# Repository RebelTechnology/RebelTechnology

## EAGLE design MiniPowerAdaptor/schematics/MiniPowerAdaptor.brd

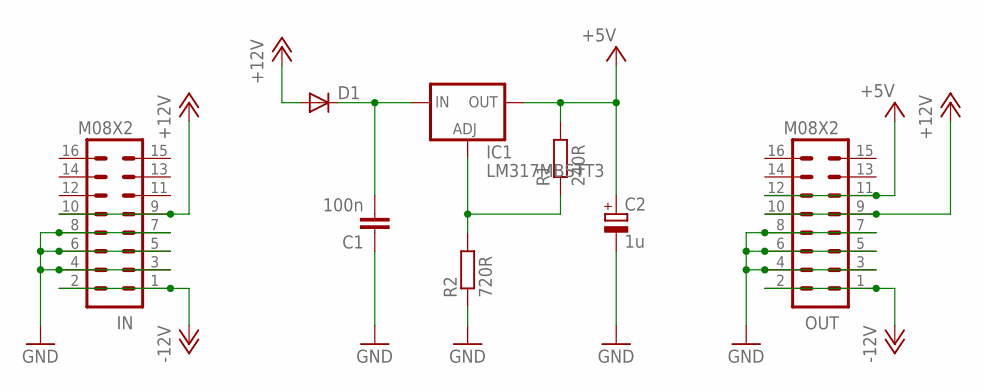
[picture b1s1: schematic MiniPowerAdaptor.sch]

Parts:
C1: 100n; C0603
C2: 1u; SANYO-OSCON_SMD_A5
D1: DIODESMA; SMA-DIODE
IC1: LM317MBSTT3; SOT223
IN: M08X2; 2X8
OUT: M08X2; 2X8
R1: 240R; 0603
R2: 720R; 0603

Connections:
+5V: C2.+, IC1.4 (OUT), OUT.11, OUT.12, R1.2
+12V: D1.A, IN.9, IN.10, OUT.9, OUT.10
-12V: IN.1, IN.2, OUT.1, OUT.2
GND: C1.1, C2.-, IN.3, IN.4, IN.5, IN.6, IN.7, IN.8, OUT.3, OUT.4, OUT.5, OUT.6, OUT.7, OUT.8, R2.1
unnamed: IC1.1 (ADJ), R1.1, R2.2
unnamed: C1.2, D1.C, IC1.3 (IN)

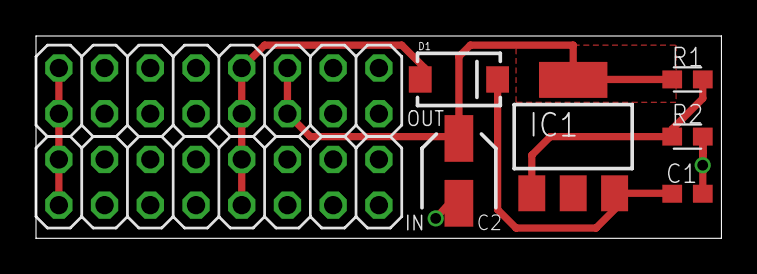
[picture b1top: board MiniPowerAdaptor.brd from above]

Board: 2 copper layers, 38.1 x 11.2 mm, 8 parts (0 on the bottom side), 6 nets.

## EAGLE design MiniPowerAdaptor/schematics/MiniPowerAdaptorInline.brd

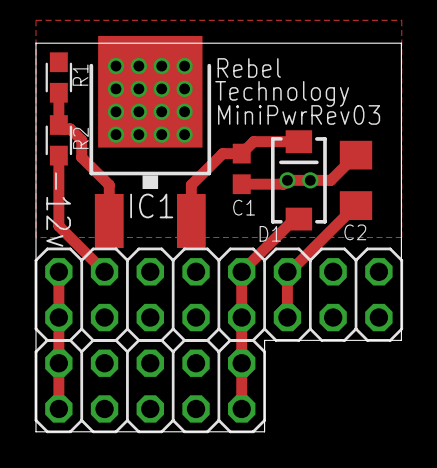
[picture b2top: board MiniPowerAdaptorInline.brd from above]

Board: 2 copper layers, 20.3 x 21.6 mm, 8 parts (0 on the bottom side), 6 nets.

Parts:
C1: 100n; C0603
C2: 10u; C1206
D1: S1J; SMA-DIODE
IC1: LM317; DPACK
JP1: 2X05
OUT: M08X2; 2X8
R1: 330R; 0603
R2: 1k; 0603

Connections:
+5V: C2.1, IC1.4, OUT.11, OUT.12, R1.2
+12V: D1.A, JP1.9, JP1.10, OUT.9, OUT.10
-12V: JP1.1, JP1.2, OUT.1, OUT.2
GND: C1.1, C2.2, JP1.3, JP1.4, JP1.5, JP1.6, JP1.7, JP1.8, OUT.3, OUT.4, OUT.5, OUT.6, OUT.7, OUT.8, R2.1
unnamed: IC1.1, R1.1, R2.2
unnamed: C1.2, D1.C, IC1.3

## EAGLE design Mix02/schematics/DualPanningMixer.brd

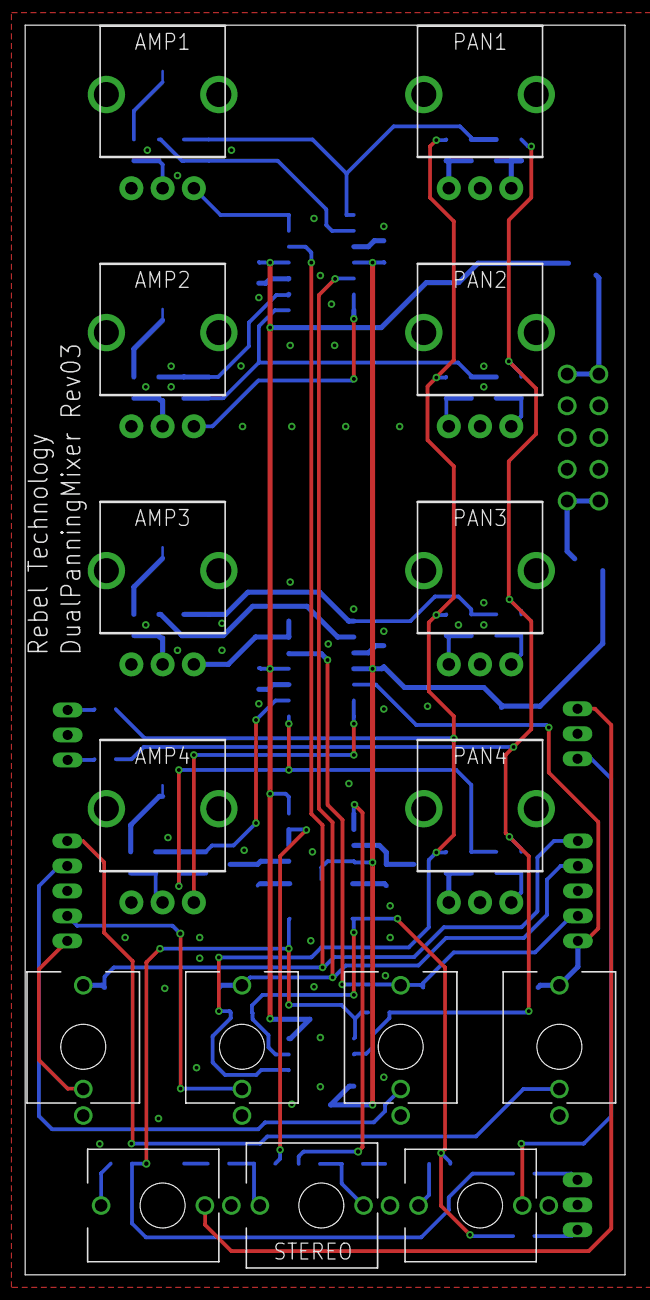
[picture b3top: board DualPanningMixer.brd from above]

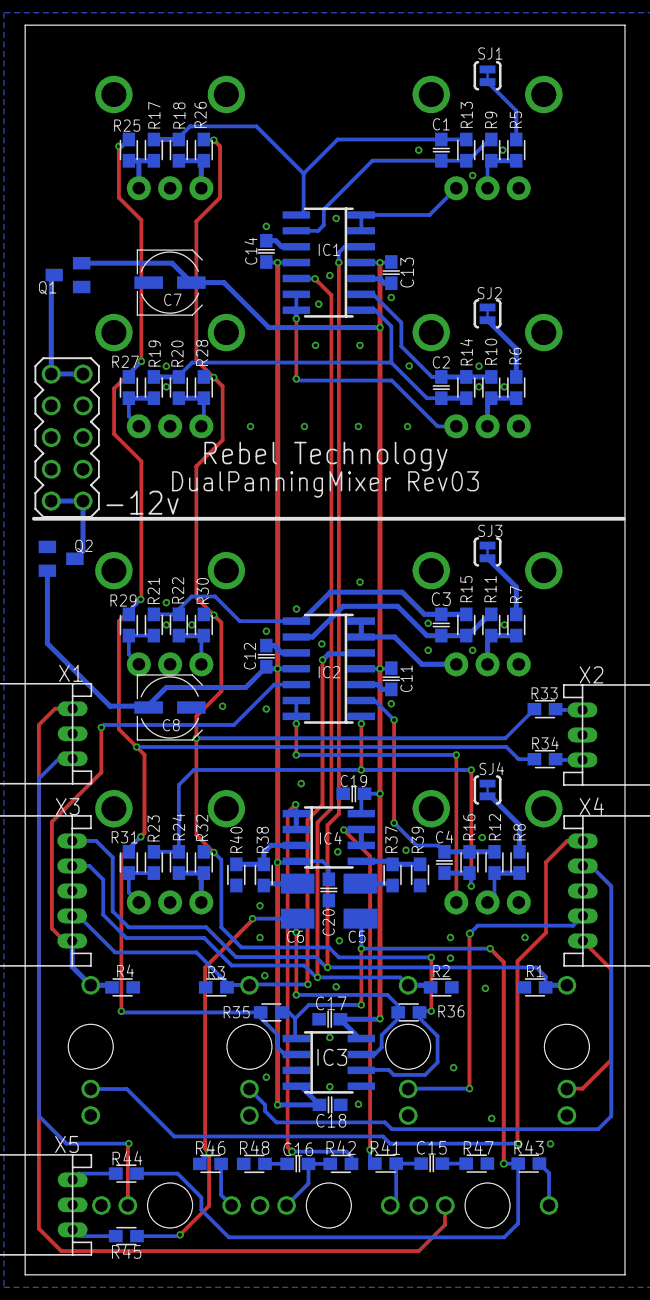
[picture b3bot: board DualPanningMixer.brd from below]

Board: 2 copper layers, 48.0 x 100.0 mm, 97 parts (82 on the bottom side), 63 nets.

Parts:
AMP1, AMP2, AMP3, AMP4: POT-ALPS-RK09L1140
C1, C2, C3, C4: 10p; C0603
C5, C6: 1u Polyester; C1210
C7, C8: 47u; UD-5X5,8_NICHICON
C11, C12, C13, C14, C17, C18, C19, C20: 100n; C0603
C15, C16: 47n; C0603
IC1, IC2: TL074; SO14
IC3: TL072; SO08
IC4: OPA1678; SO08
IN1, IN2, IN3, IN4: THONKICONN
OUTHP: THONKICONN_STEREO
OUTL: THONKICONN
OUTR: THONKICONN
PAN1, PAN2, PAN3, PAN4: POT-ALPS-RK09L1140
Q1: BSS84; SOT23
Q2: BSS123; SOT23
R1, R2, R3, R4: 1M; 0603
R5, R6, R7, R8: 2k7; 0603
R9, R10, R11, R12, R17, R18, R19, R20, R21, R22, R23, R24, R25, R26, R27, R28, R29, R30, R31, R32: 10k; 0603
R13, R14, R15, R16, R35, R36: 22k; 0603
R33, R34: 18k; 0603
R37, R38: 2k; 0603
R39, R40: 1k; 0603
R41, R42, R47, R48: 10R; 0603
R43, R44, R45, R46: 100R; 0603
SJ1, SJ2, SJ3, SJ4: SOLDERJUMPERTRACE; SJ_2S-TRACE
SV1: MA05-2
X1, X2, X5: CON-JST_PH_3W
X3, X4: CON-JST_PH_5W

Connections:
+12V: C7.+, C11.2, C13.2, C17.2, C19.1, IC1.4, IC2.4, IC3.8, IC4.8, Q1.2
-12V: C8.-, C12.2, C14.2, C18.2, C20.1, IC1.11, IC2.11, IC3.4, IC4.4, Q2.2
GND: AMP1.1, AMP1.P$5, AMP1.P$6, AMP2.1, AMP2.P$5, AMP2.P$6, AMP3.1, AMP3.P$5, AMP3.P$6, AMP4.1, AMP4.P$5, AMP4.P$6, C7.-, C8.+, C11.1, C12.1, C13.1, C14.1, C17.1, C18.1, C19.2, C20.2, IC1.3, IC1.10, IC2.3, IC2.10, IC3.3, IC3.5, IN1.P$1, IN2.P$1, IN3.P$1, IN4.P$1, OUTHP.P$1, OUTL.P$1, OUTR.P$1, PAN1.2, PAN1.P$5, PAN1.P$6, PAN2.2, PAN2.P$5, PAN2.P$6, PAN3.2, PAN3.P$5, PAN3.P$6, PAN4.2, PAN4.P$5, PAN4.P$6, Q1.1, Q2.1, R1.1, R2.1, R3.1, R4.1, R39.1, R40.1, R47.1, R48.1, SJ1.1, SJ2.1, SJ3.1, SJ4.1, SV1.3, SV1.4, SV1.5, SV1.6, SV1.7, SV1.8, X1.P2, X2.P2, X3.P3, X4.P3, X5.P2
LAB: IC3.2, R25.1, R27.1, R29.1, R31.1, R34.2, R35.1
L_OUT: C15.1, OUTHP.P$3, R41.1
MONO1: AMP1.3, IC1.6, IC1.7
MONO1_F: IC1.5, IN1.P$3, R1.2, X3.P1
MONO2: AMP2.3, IC1.13, IC1.14
MONO2_F: IC1.12, IN2.P$3, R2.2, X3.P2
MONO3: AMP3.3, IC2.6, IC2.7
MONO3_F: IC2.5, IN3.P$3, R3.2, X3.P4
MONO4: AMP4.3, IC2.13, IC2.14
MONO4_F: IC2.12, IN4.P$3, R4.2, X3.P5
unnamed: AMP4.2, R8.2, R12.1
unnamed: IN2.P$2, X4.P2
unnamed: C5.1, IC3.1, R35.2, R43.1, R44.1
unnamed: IN1.P$2, X4.P1
unnamed: C6.1, IC3.7, R36.2, R45.1, R46.1
unnamed: IN3.P$2, X4.P4
unnamed: IC4.3, R38.1, R40.2
unnamed: AMP1.2, R5.2, R9.1
unnamed: C1.2, IC1.9, R9.2, R13.1
unnamed: AMP3.2, R7.2, R11.1
unnamed: AMP2.2, R6.2, R10.1
unnamed: R5.1, SJ1.2
unnamed: IC4.5, R37.1, R39.2
unnamed: R33.1, X2.P3
unnamed: IN4.P$2, X4.P5
unnamed: R6.1, SJ2.2
unnamed: PAN1.1, R18.1, R26.2
unnamed: PAN1.3, R17.1, R25.2
unnamed: R7.1, SJ3.2
unnamed: R8.1, SJ4.2
unnamed: C1.1, IC1.8, R13.2, R17.2, R18.2
unnamed: R34.1, X2.P1
unnamed: C4.1, IC2.1, R16.2, R23.2, R24.2
unnamed: C2.1, IC1.1, R14.2, R19.2, R20.2
unnamed: PAN2.3, R19.1, R27.2
unnamed: OUTL.P$3, R43.2
unnamed: PAN2.1, R20.1, R28.2
unnamed: PAN3.3, R21.1, R29.2
unnamed: C3.1, IC2.8, R15.2, R21.2, R22.2
unnamed: PAN3.1, R22.1, R30.2
unnamed: PAN4.3, R23.1, R31.2
unnamed: OUTR.P$3, R46.2
unnamed: PAN4.1, R24.1, R32.2
unnamed: C16.2, R48.2
unnamed: C2.2, IC1.2, R10.2, R14.1
unnamed: Q2.3, SV1.1, SV1.2
unnamed: C3.2, IC2.9, R11.2, R15.1
unnamed: Q1.3, SV1.9, SV1.10
unnamed: C4.2, IC2.2, R12.2, R16.1
unnamed: C15.2, R47.2
unnamed: C5.2, R37.2
unnamed: IC4.6, IC4.7, R41.2
unnamed: IC4.1, IC4.2, R42.2
unnamed: C6.2, R38.2
OUT_NS_L: R44.2, X5.P1
OUT_NS_R: R45.2, X5.P3
OUT_SW_L: OUTL.P$2, X1.P1
OUT_SW_R: OUTR.P$2, X1.P3
RAB: IC3.6, R26.1, R28.1, R30.1, R32.1, R33.2, R36.1
R_OUT: C16.1, OUTHP.P$2, R42.1

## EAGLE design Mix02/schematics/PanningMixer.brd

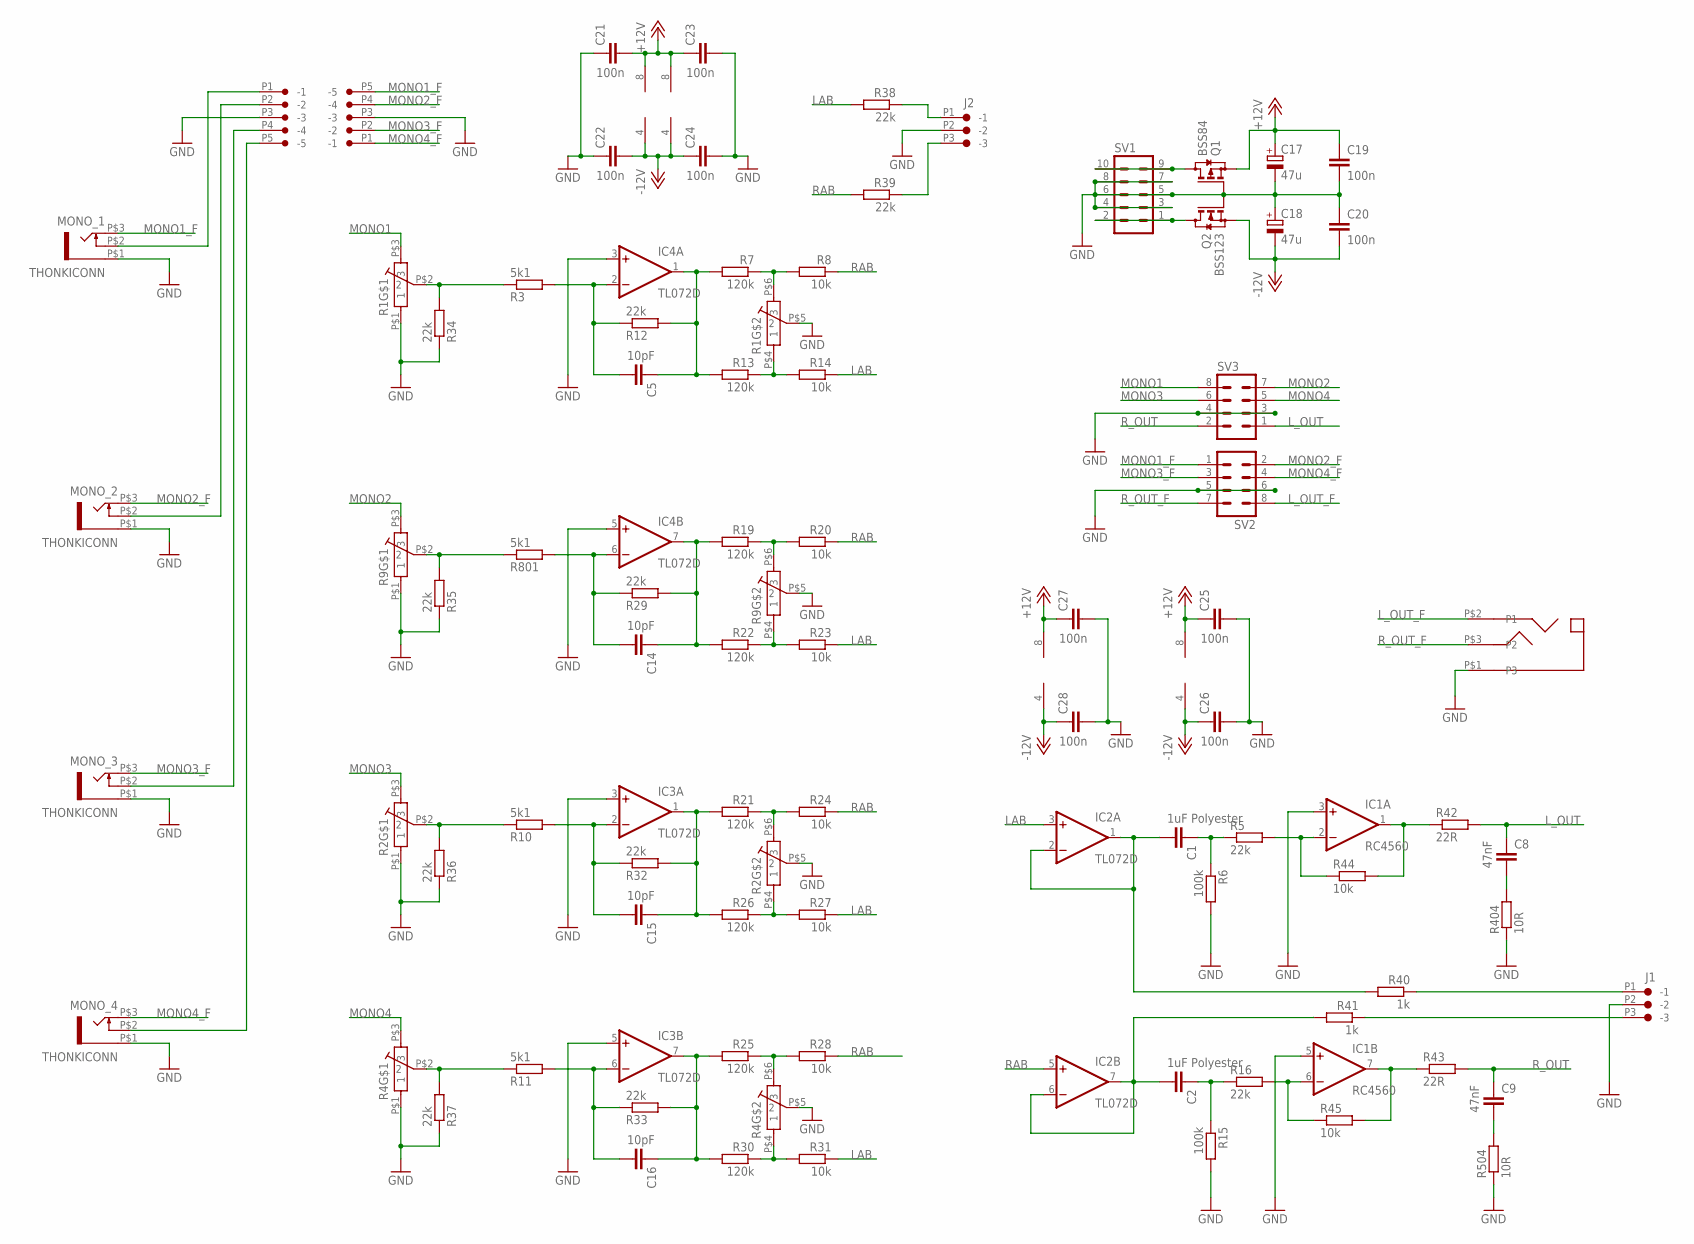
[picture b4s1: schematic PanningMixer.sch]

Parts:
C1, C2: 1uF Polyester; C1210
C5, C14, C15, C16: 10pF; C0603
C8, C9: 47nF; C0603
C17, C18: 47u; PANASONIC_B
C19, C20, C21, C22, C23, C24, C25, C26, C27, C28: 100n; C0603
IC1: RC4560; SO08
IC2, IC3, IC4: TL072D; SO08
J1, J2: CON-JST_PH_3W
MONO_1, MONO_2, MONO_3, MONO_4: THONKICONN
Q1: BSS84; SOT23
Q2: BSS123; SOT23
R1, R2, R4, R9: POT-ALPHA_DUAL_9MM; POT-ALPA_DUAL_9MM
R3, R10, R11, R801: 5k1; 0603
R5, R12, R16, R29, R32, R33, R34, R35, R36, R37, R38, R39: 22k; 0603
R6, R15: 100k; 0603
R7, R13, R19, R21, R22, R25, R26, R30: 120k; 0603
R8, R14, R20, R23, R24, R27, R28, R31, R44, R45: 10k; 0603
R40, R41: 1k; 0603
R42, R43: 22R; 0603
R404, R504: 10R; 0603
SV1: MA05-2
SV2, SV3: MA04-2
U1: CON-PROSIGNAL_MJ-355W
U2, U4: CON-JST_PH_5W

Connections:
+12V: C17.+, C19.1, C21.2, C23.1, C25.1, C27.1, IC1.8 (V+), IC2.8 (V+), IC3.8 (V+), IC4.8 (V+), Q1.2 (S)
-12V: C18.-, C20.2, C22.2, C24.1, C26.1, C28.1, IC1.4 (V-), IC2.4 (V-), IC3.4 (V-), IC4.4 (V-), Q2.2 (S)
GND: C17.-, C18.+, C19.2, C20.1, C21.1, C22.1, C23.2, C24.2, C25.2, C26.2, C27.2, C28.2, IC1.3 (+IN), IC1.5 (+IN), IC3.3 (+IN), IC3.5 (+IN), IC4.3 (+IN), IC4.5 (+IN), J1.P2 (-2), J2.P2 (-2), Q1.1 (G), Q2.1 (G), R1.P$1 (1), R1.P$5 (2), R2.P$1 (1), R2.P$5 (2), R4.P$1 (1), R4.P$5 (2), R6.2, R9.P$1 (1), R9.P$5 (2), R15.2, R34.1, R35.1, R36.1, R37.1, R404.1, R504.1, SV1.3, SV1.4, SV1.5, SV1.6, SV1.7, SV1.8, SV3.3, SV3.4
GND_A: MONO_1.P$1 (5), MONO_2.P$1 (5), MONO_3.P$1 (5), MONO_4.P$1 (5), SV2.5, SV2.6, U1.P$1 (P3), U2.P3 (-3), U4.P3 (-3)
LAB: IC2.3 (+IN), R14.1, R23.1, R27.1, R31.1, R38.2
L_OUT: C8.1, R42.2, SV3.1
L_OUT_F: SV2.8, U1.P$2 (P1)
MONO1: R1.P$3 (3), SV3.8
MONO1_F: MONO_1.P$3 (3), SV2.1, U4.P5 (-5)
MONO2: R9.P$3 (3), SV3.7
MONO2_F: MONO_2.P$3 (3), SV2.2, U4.P4 (-4)
MONO3: R2.P$3 (3), SV3.6
MONO3_F: MONO_3.P$3 (3), SV2.3, U4.P2 (-2)
MONO4: R4.P$3 (3), SV3.5
MONO4_F: MONO_4.P$3 (3), SV2.4, U4.P1 (-1)
unnamed: R4.P$2 (2), R11.1, R37.2
unnamed: MONO_2.P$2 (4), U2.P2 (-2)
unnamed: MONO_1.P$2 (4), U2.P1 (-1)
unnamed: C1.1, R5.1, R6.1
unnamed: MONO_3.P$2 (4), U2.P4 (-4)
unnamed: IC1.2 (-IN), R5.2, R44.1
unnamed: R1.P$2 (2), R3.1, R34.2
unnamed: C5.2, IC4.2 (-IN), R3.2, R12.1
unnamed: R2.P$2 (2), R10.1, R36.2
unnamed: R9.P$2 (2), R35.2, R801.1
unnamed: C9.2, R504.2
unnamed: J2.P1 (-1), R38.1
unnamed: MONO_4.P$2 (4), U2.P5 (-5)
unnamed: J1.P1 (-1), R40.1
unnamed: R1.P$4 (1), R13.1, R14.2
unnamed: R1.P$6 (3), R7.1, R8.2
unnamed: J1.P3 (-3), R41.1
unnamed: C8.2, R404.2
unnamed: C2.1, R15.1, R16.1
unnamed: C5.1, IC4.1 (OUT), R7.2, R12.2, R13.2
unnamed: J2.P3 (-3), R39.1
unnamed: C16.1, IC3.7 (OUT), R25.2, R30.2, R33.2
unnamed: C14.1, IC4.7 (OUT), R19.2, R22.2, R29.2
unnamed: IC1.1 (OUT), R42.1, R44.2
unnamed: IC1.6 (-IN), R16.2, R45.1
unnamed: C1.2, IC2.1 (OUT), IC2.2 (-IN), R40.2
unnamed: IC1.7 (OUT), R43.1, R45.2
unnamed: C2.2, IC2.6 (-IN), IC2.7 (OUT), R41.2
unnamed: R9.P$6 (3), R19.1, R20.2
unnamed: R9.P$4 (1), R22.1, R23.2
unnamed: R2.P$6 (3), R21.1, R24.2
unnamed: C15.1, IC3.1 (OUT), R21.2, R26.2, R32.2
unnamed: R2.P$4 (1), R26.1, R27.2
unnamed: R4.P$6 (3), R25.1, R28.2
unnamed: R4.P$4 (1), R30.1, R31.2
unnamed: C14.2, IC4.6 (-IN), R29.1, R801.2
unnamed: Q2.3 (D), SV1.1, SV1.2
unnamed: C15.2, IC3.2 (-IN), R10.2, R32.1
unnamed: Q1.3 (D), SV1.9, SV1.10
unnamed: C16.2, IC3.6 (-IN), R11.2, R33.1
RAB: IC2.5 (+IN), R8.1, R20.1, R24.1, R28.1, R39.2
R_OUT: C9.1, R43.2, SV3.2
R_OUT_F: SV2.7, U1.P$3 (P2)

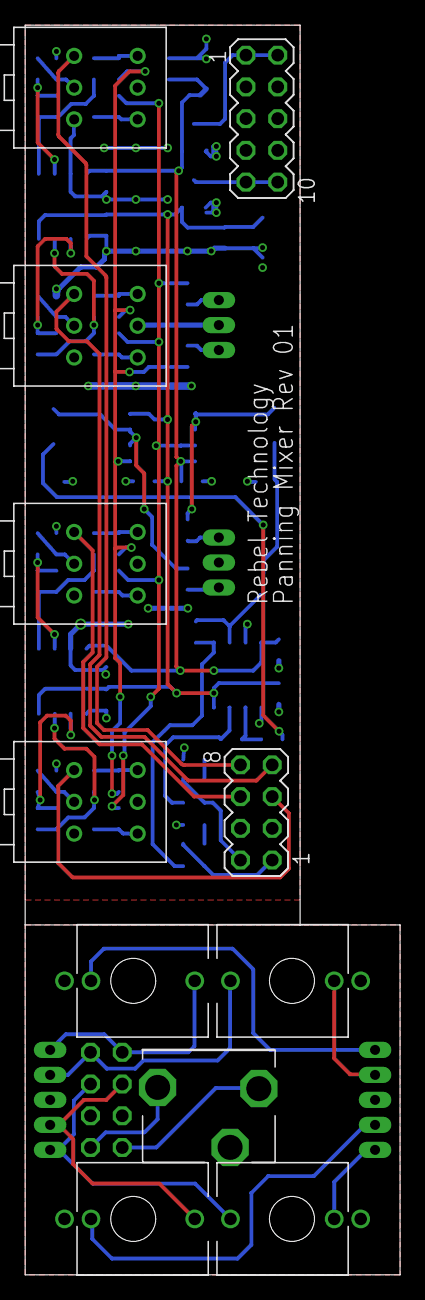
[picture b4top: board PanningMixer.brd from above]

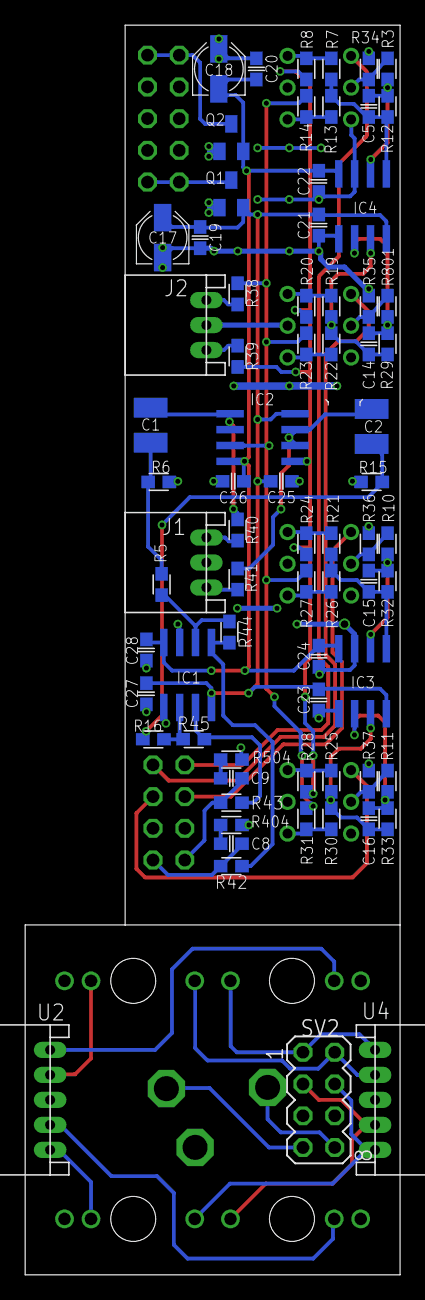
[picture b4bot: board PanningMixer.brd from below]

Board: 2 copper layers, 30.0 x 100.0 mm, 84 parts (73 on the bottom side), 58 nets.

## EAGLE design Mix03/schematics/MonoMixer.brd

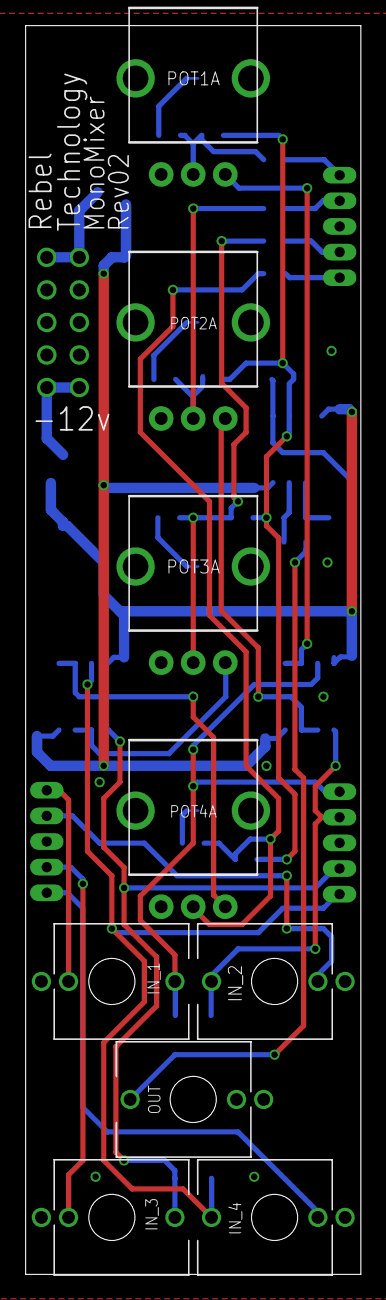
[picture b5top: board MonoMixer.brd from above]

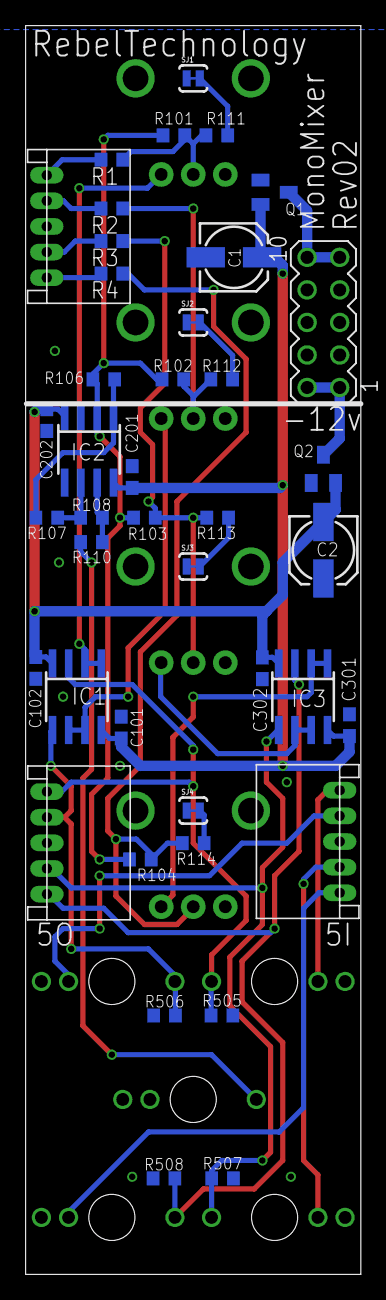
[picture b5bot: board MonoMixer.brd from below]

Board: 2 copper layers, 26.2 x 97.5 mm, 50 parts (41 on the bottom side), 34 nets.

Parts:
C1, C2: 10u; 153CLV-0505
C101, C102, C201, C202, C301, C302: 100n; C0603
IC1, IC2, IC3: TL072D; SO08
IN_1, IN_2, IN_3, IN_4: THONKICONN
OUT: THONKICONN
POT1A, POT2A, POT3A, POT4A: POT-ALPS-RK09L1140
Q1: SI2309CDS; SOT23
Q2: BSS123; SOT23
R1, R2, R3, R4, R110: 1k; R0603
R101, R102, R103, R104, R106, R108: 10k; R0603
R107: 5k1; R0603
R111, R112, R113, R114: 2k7; R0603
R505, R506, R507, R508: 1M; R0603
SJ1, SJ2, SJ3, SJ4: SOLDERJUMPERTRACE; SJ_2S-TRACE
SV1: MA05-2
U2, U3, U4: CON-JST_PH_5W

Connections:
+12V: C1.+, C101.1, C201.1, C301.1, IC1.8, IC2.8, IC3.8, Q1.2
-12V: C2.-, C102.1, C202.1, C302.1, IC1.4, IC2.4, IC3.4, Q2.2
GND: C1.-, C2.+, C101.2, C102.2, C201.2, C202.2, C301.2, C302.2, IC2.3, IC2.5, IN_1.P$1, IN_2.P$1, IN_3.P$1, IN_4.P$1, OUT.P$1, POT1A.1, POT1A.P$5, POT1A.P$6, POT2A.1, POT2A.P$5, POT2A.P$6, POT3A.1, POT3A.P$5, POT3A.P$6, POT4A.1, POT4A.P$5, POT4A.P$6, Q1.1, Q2.1, R505.2, R506.2, R507.2, R508.2, SJ1.1, SJ2.1, SJ3.1, SJ4.1, SV1.3, SV1.4, SV1.5, SV1.6, SV1.7, SV1.8, U2.P3, U3.P3, U4.P3
IN_1: IC1.3, IN_1.P$3, R505.1, U3.P5
IN_2: IC1.5, IN_2.P$3, R506.1, U3.P4
IN_3: IC3.5, IN_3.P$3, R507.1, U3.P2
IN_4: IC3.3, IN_4.P$3, R508.1, U3.P1
IN_SW_1: IN_1.P$2, U4.P1
IN_SW_2: IN_2.P$2, U4.P2
IN_SW_3: IN_3.P$2, U4.P4
IN_SW_4: IN_4.P$2, U4.P5
unnamed: Q2.3, SV1.1, SV1.2
unnamed: R1.2, U2.P5
unnamed: R2.2, U2.P4
unnamed: R3.2, U2.P2
unnamed: R4.2, U2.P1
unnamed: IC2.7, R108.2, R110.1
unnamed: OUT.P$3, R110.2
unnamed: IC2.2, R101.1, R102.1, R103.1, R104.1, R106.1
unnamed: IC2.1, R106.2, R107.1
unnamed: Q1.3, SV1.9, SV1.10
unnamed: R111.2, SJ1.2
unnamed: IC2.6, R107.2, R108.1
unnamed: R112.2, SJ2.2
unnamed: R113.2, SJ3.2
unnamed: R114.2, SJ4.2
unnamed: POT1A.2, R1.1, R101.2, R111.1
unnamed: IC3.1, IC3.2, POT4A.3
unnamed: IC3.6, IC3.7, POT3A.3
unnamed: IC1.6, IC1.7, POT2A.3
unnamed: IC1.1, IC1.2, POT1A.3
unnamed: POT4A.2, R4.1, R104.2, R114.1
unnamed: POT3A.2, R3.1, R103.2, R113.1
unnamed: POT2A.2, R2.1, R102.2, R112.1

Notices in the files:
parts and their libraries:
SparkFun: Licensing: CC v3.0 Share-Alike You are welcome to use this library for commercial purposes.
SparkFun-Connectors: Licensing: Creative Commons ShareAlike 4.0 International - https://creativecommons.org/licenses/by-sa/4.0
